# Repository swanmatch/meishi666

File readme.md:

# meishi666(めいしとらいしっくす)ビルドガイド
## 材料

| 品目 | 数量 | 仕入先 |
| - | - | - |
| PCB | 1枚 | 魔王 |
| スルーホールダイオード(1N4148) | 7本(感圧スピーカ利用時8本) | 秋月電子 |
| ProMicro | 1個 | TalpKeyboard,遊舎工房 |
| タクトスイッチ | 1個 | 秋月電子、Aitendo |
| MX互換スイッチ(5pin推奨) | 7個 | TalpKeyboard,遊舎工房 |
| キーキャップ | 7個 | TalpKeyboard,遊舎工房 |
| LED(SK6812mini)(オプション) | 7個 | 遊舎工房,ピカリ館 |
| OLEDディスプレイ(オプション) | 1個 | 遊舎工房 |
| 感圧スピーカ(オプション) | 1個 | 秋月電子 |
| 1KΩ抵抗(スピーカ利用時) | 1個 | 秋月電子 |
私自身あまり順番とか気にせず気分で作ってるので、ちょっと写真の順番があべこべしてます。
気にしないでください。

## 1. LEDの実装(オプション、難易度高め)
1. 基板側の白い四角で囲んであるパッドに、LEDの一番大きいパッドを合わせるようにします。

2. 温度調整機能付きはんだごてで220℃くらいに設定します。(わりとすぐ壊れます)
3. パッド2個位ずつすばやくはんだジャンパーしていきます。(全部連続でやっていくと温度が上がって破損の危険が高まります)

## 2. ダイオードの実装

1. LightSideから黒いほうが左を向くように差し込みます。(ちょっときつい)

2. マスキングテープで動かないよう固定して、DarkSideに裏返します。

3. 足を0.5～1mmくらい残してニッパーで切ります。
4. はんだ付けします。

#### SwanTips
    * ダイオードの向きはキットによって上向き下向き左向き右向き斜めなどいろいろです。矢印向いてるほうに線を向けるように覚えてください。
    * ダイオードの向き全部間違えっちゃたーなんてときもどうか焦らず。ファームウェアでキースキャンの方向を変えればそのまま使えます。(Col2RowとかRow2Colとか宣言するだけ)
    * DarkSideから挿してもいいですが今回はトッププレート、ボトムプレートなしなので、表から挿したほうが空間に余裕があるのでおすすめしてます。

## 3. 感圧スピーカの実装(オプション)
1. 配線の都合でこれだけダイオードは右向きなので注意してください。スイッチのダイオードと同様でOKです。
2. 1KΩ抵抗を付けます。これは向きはないです。
3. 左側のパッドに予備ハンダを盛っておきます。

4. ピンセットで感圧スピーカ本体に軽く押さえつけなら、予備ハンダを溶かします。向きはないですたぶん。

5. 右のパッドにもはんだを流し込みます。

## 4. ProMicroの実装(ここだけめっちゃ慎重に!取り返しが付きません。不安なら聞いて!!)
1. LightSideからピンソケットをはめます。足が長いほうが下です。
2. ProMicroを上に重ねます。部品がたくさんくっついている方が下で、左(外側)にUSBの差込口が向くように。お願いします。。。

3. 浮いていないことを確認してはんだづけしていきます。先に両端のピンをはんだづけして、浮いていないことを確認して他をつけるのがよいです。

4. 裏返してProMicroを奥まで差し込んで、表面同様はんだづけします。

#### SwanTips
    * プロマイクロ自体の裏表、向き、基盤の裏につけるか表につけるかなどもキットによってまちまちです。
    しかも間違えて付けちゃうとリカバリがめちゃくちゃ大変です。
    ここだけはビルドガイドやフットプリントをよく見て確実に作業してください。
    とくにMCUをスイッチの裏につけるタイプ、Mint,ErgoDashなどはPromicroをつける前にスイッチ不良がないか確認してください。
    * USBの差込口は少しもげやすいです。実はUSBの仕様としてある程度もげやすくしないといけないのです。
    とはいえ高級なスイッチをはんだづけしたキーボードがUSB差込み口で無駄になるのはなんとも辛いので、エポキシ接着剤で事前に固めておくのがベターです。
    エポキシ接着剤は100円ショップに売っていて、一個変えば一生分のキーボードを作れる分はあるかと。
    * もげたPromicroを交換できるようにするコンスルーというピンヘッダがあって、ちょっとお高いけどとても便利です。
    * マグネットケーブルももげ対策には効果的です。

## 5. OLEDディスプレイの実装(オプション)
1. ピンソケットをはんだ付けします。マスキングテープかその他創意工夫を凝らして浮かないように気をつけてください。(←めんどくさくなってきた)
2. ピンソケットにピンヘッダを差し込みます。
3. OLEDディスプレイをはめて、余分な足をニッパーで切ってからはんだ付けします。

## 6. スイッチの実装
1. スイッチをはめます。ここはハマるようにしかはまらないので安心して。基板がぐらつくと思うのでスイッチをかませるとよいです。
片方のピンだけはんだ付けした段階で浮いてないか確認してください。浮いている場合LightSideからスイッチを指で上げながらはんだごてを当て直すとよいです。
2. もう片方のピンもはんだ付けします

#### SwanTips
    * 一般的なキーボードはスイッチを固定するトッププレートというものがありますが、今回は入門用ということでトッププレート無しです。
    トッププレートがないので、代わりにスイッチが回転しないように5pinのスイッチを使うのが良いです。
    * 一般的な5pinスイッチはPCBに刺さってはんだ付けしなくてもある程度固定されるようできているのですが、KailhPro5Pinはゆるゆるでした。はんだ付けしにくくてごめんなさい…！
    * 実は今回付けたスイッチの方向は一般的なCherry互換のスイッチと上下逆さまです。一般的なバックライト用の透過刻印のキーキャップが上部が光っていたほうがバエるので、バックライト対応のキーボードはこの向きが多いです。
    逆さまで問題になることはほとんどありませんが、CherryProfileというプロファイルのキーキャップだけ、若干スイッチと干渉するのでご注意あれ。

## 7. リセットスイッチの実装
1. リセットスイッチをLightSideからはめ込んで、DarkSideからはんだ付けします。(たぶんマスキングテープとかなくても問題ないかとー)

## 8. ファームウェアの書き込み
Windowsの方はMsys2という環境を入れてから臨むのがよいらしいです。

```sh
# 初回のみ
git clone https://github.com/swanmatch/qmk_firmware
cd qmk_firmware
sh util/qmk_install.sh
make git-submodule
# 初回のみ終わり
# Ubuntuなどの場合、頭にsudoを付ける必要があります。
make meishi666:default:avrdude
```

キーの割当を変更したい場合、下記をいじるとだいたい解決します。
https://github.com/swanmatch/qmk_firmware/blob/master/keyboards/meishi666/keymaps/default/keymap.c

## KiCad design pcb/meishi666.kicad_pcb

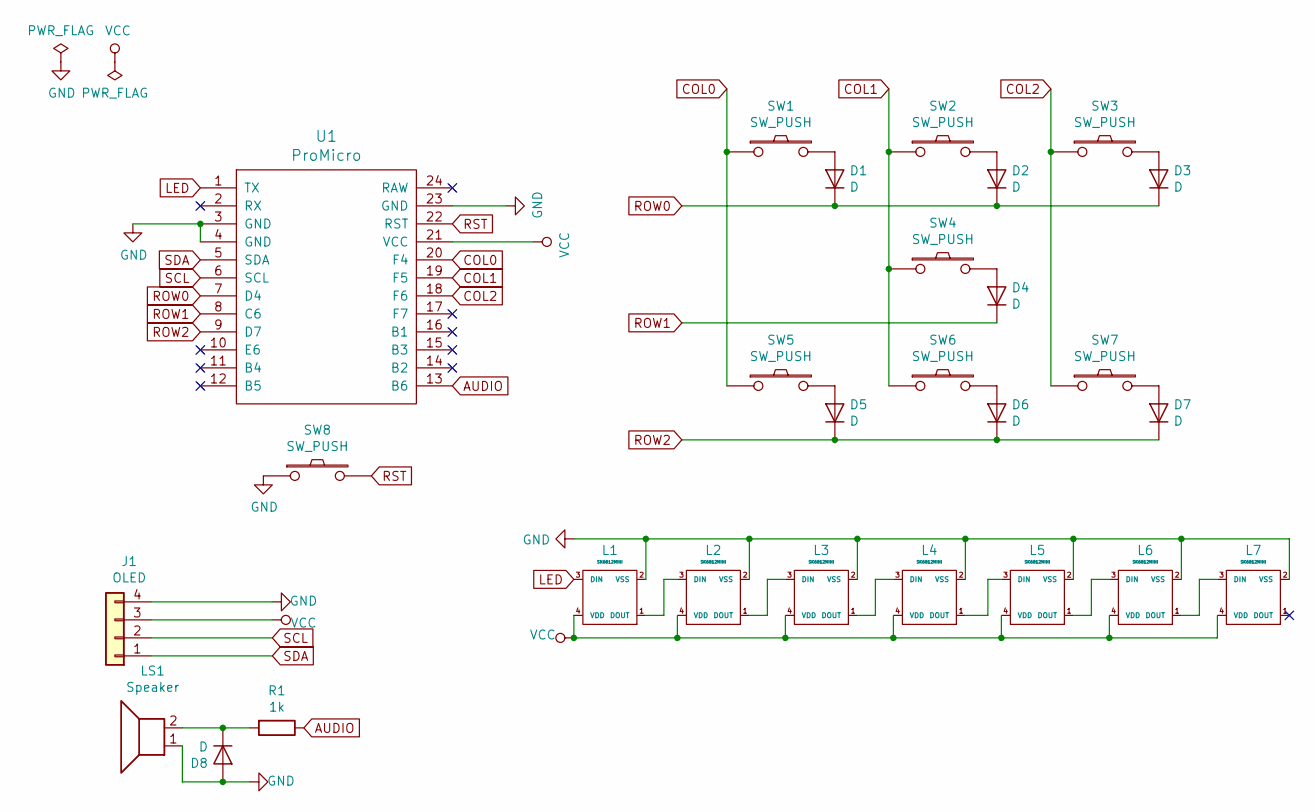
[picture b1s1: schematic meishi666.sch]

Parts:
D1, D2, D3, D4, D5, D6, D7, D8: D; Diode-hybrid-3pad
J1: OLED
L1, L2, L3, L4, L5, L6, L7: SK6812MINI; SK6812MINI_rev
LS1: Speaker; PKLCS1212E4001_HandSoldering
R1: 1k; Resistor-Hybrid
SW1, SW2, SW3, SW4, SW5, SW6, SW7: SW_PUSH; MX_PCB_100H
SW8: SW_PUSH; ResetSW
U1: ProMicro; ArduinoProMicro

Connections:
AUDIO: R1.1, U1.13 (B6)
COL0: SW1.1, SW5.1, U1.20 (F4)
COL1: SW2.1, SW4.1, SW6.1, U1.19 (F5)
COL2: SW3.1, SW7.1, U1.18 (F6)
GND: D8.2 (A), J1.4, L1.2 (VSS), L2.2 (VSS), L3.2 (VSS), L4.2 (VSS), L5.2 (VSS), L6.2 (VSS), L7.2 (VSS), LS1.1, SW8.1, U1.3 (GND), U1.4 (GND), U1.23 (GND); also elsewhere on the board
LED: L1.3 (DIN), U1.1 (TX)
unnamed: D1.2 (A), SW1.2
unnamed: D2.2 (A), SW2.2
unnamed: D3.2 (A), SW3.2
unnamed: D4.2 (A), SW4.2
unnamed: D5.2 (A), SW5.2
unnamed: D6.2 (A), SW6.2
unnamed: D7.2 (A), SW7.2
unnamed 13: D8.1 (K), LS1.2, R1.2; also elsewhere on the board
unnamed: L1.1 (DOUT), L2.3 (DIN)
unnamed: L2.1 (DOUT), L3.3 (DIN)
unnamed: L3.1 (DOUT), L4.3 (DIN)
unnamed: L4.1 (DOUT), L5.3 (DIN)
unnamed: L5.1 (DOUT), L6.3 (DIN)
unnamed: L6.1 (DOUT), L7.3 (DIN)
ROW0: D1.1 (K), D2.1 (K), D3.1 (K), U1.7 (D4)
ROW1: D4.1 (K), U1.8 (C6)
ROW2: D5.1 (K), D6.1 (K), D7.1 (K), U1.9 (D7)
RST: SW8.2, U1.22 (RST)
SCL: J1.2, U1.6 (SCL)
SDA: J1.1, U1.5 (SDA)
VCC: J1.3, L1.4 (VDD), L2.4 (VDD), L3.4 (VDD), L4.4 (VDD), L5.4 (VDD), L6.4 (VDD), L7.4 (VDD), U1.21 (VCC)

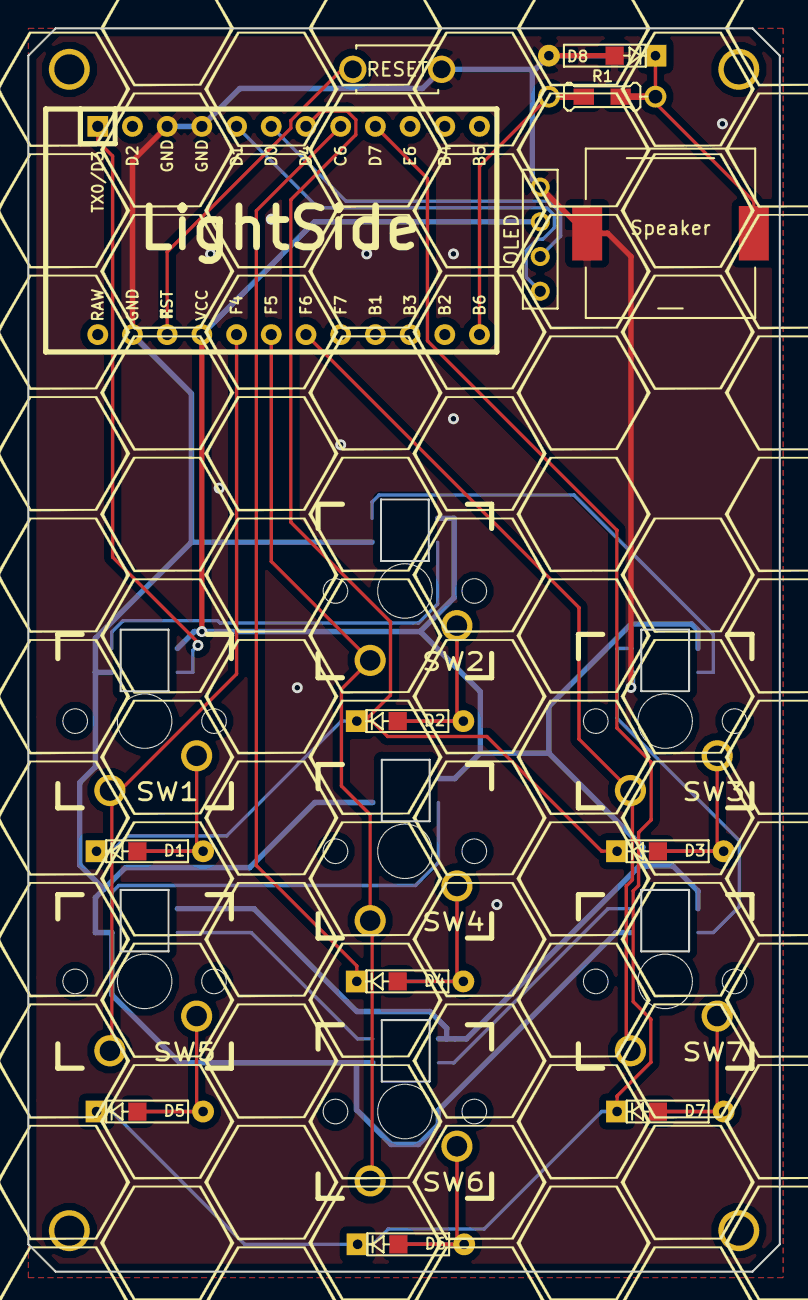
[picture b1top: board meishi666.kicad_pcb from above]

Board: 2 copper layers, 55.0 x 91.0 mm, 31 parts (1 on the bottom side), 27 nets.

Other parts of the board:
Ref0, Ref1, Ref2, Ref3: Val**; HOLE
Speaker: Speaker; PKLCS1212E4001_HandSoldering

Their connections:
GND: Speaker.1; also elsewhere on the board
unnamed 13: Speaker.2; also elsewhere on the board

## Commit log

2019-06-14 add fin picture
2019-11-12 Set theme jekyll-theme-hacker
